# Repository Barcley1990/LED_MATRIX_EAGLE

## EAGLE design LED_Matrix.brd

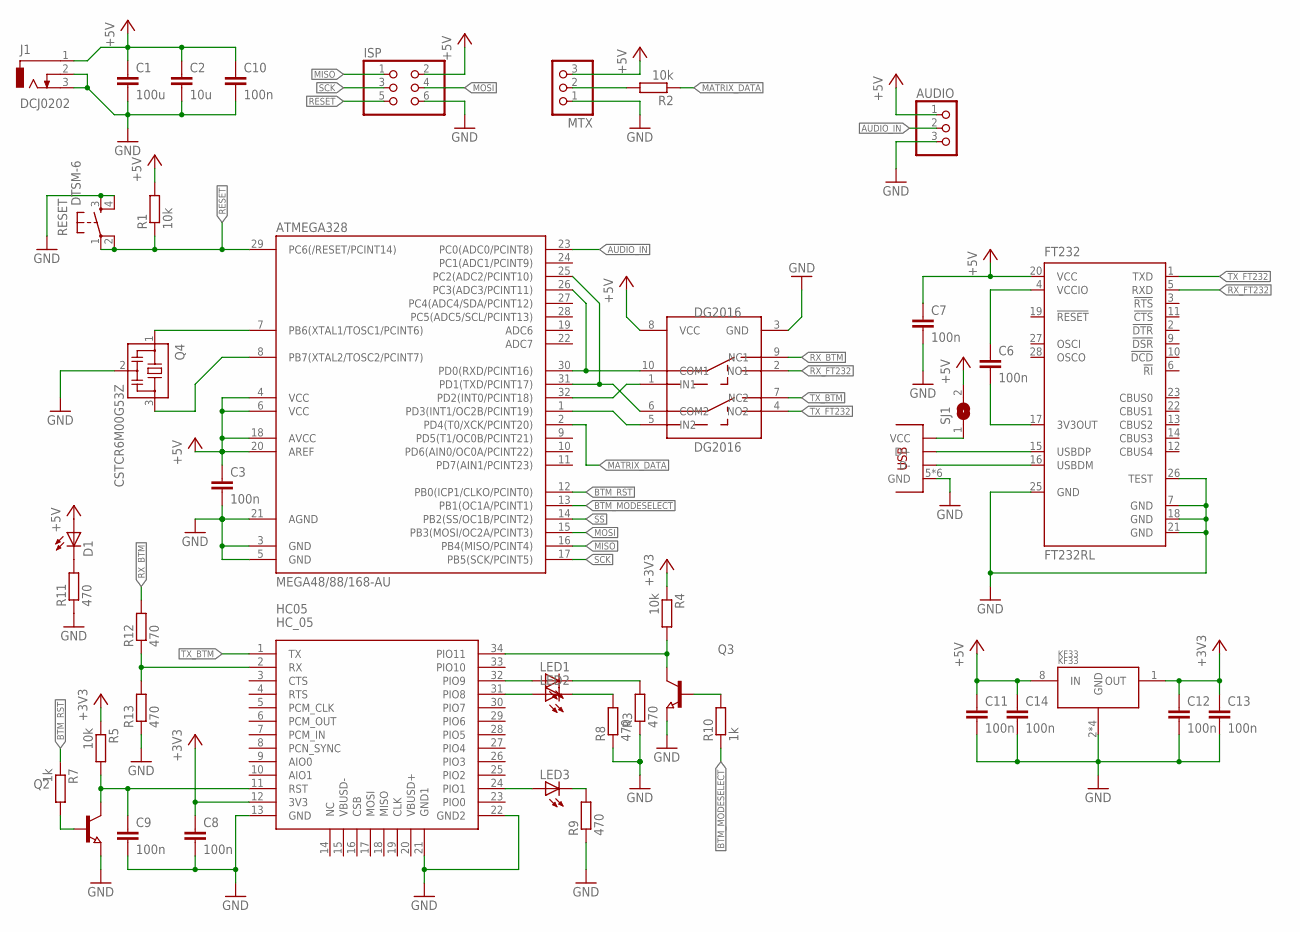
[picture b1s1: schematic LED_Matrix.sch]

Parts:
ATMEGA328: MEGA48/88/168-AU; TQFP32-08
AUDIO: PINHD-1X3; 1X03
C1: 100u; C0805
C2: 10u; C0805
C3, C6, C7, C8, C9, C10, C11, C12, C13, C14: 100n; C0805
D1: LEDSML0805; SML0805
DG2016: DG2016; MSOP10
FT232: FT232RL; SSOP28
HC05: HC_05; BLUETOOTH_SMD
ISP: PINHD-2X3; 2X03
J1: DCJ0202
KF33: KF33; SO08
LED1, LED2, LED3: LEDSML0805; SML0805
MTX: PINHD-1X3; 1X03
Q2, Q3: NPN-TRANSISTOR_SOT23; SOT23
Q4: CSTCR6M00G53Z; CSTCR6M
R1, R2, R4, R5: 10k; R0805
R3, R8, R9, R11, R12, R13: 470; R0805
R7, R10: 1k; R0805
RESET: DTSM-6
SJ1: SJ
USB: MINI_USB; USB_MINI

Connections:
+3V3: C8.1, C12.1, C13.1, HC05.12 (3V3), KF33.1 (OUT), R4.1, R5.1
+5V: ATMEGA328.4 (VCC), ATMEGA328.6 (VCC), ATMEGA328.18 (AVCC), ATMEGA328.20 (AREF), AUDIO.1, C1.1, C2.1, C3.1, C7.1, C10.1, C11.1, C14.1, D1.A, DG2016.8 (VCC), FT232.20 (VCC), ISP.2, J1.1, KF33.8 (IN), MTX.3, R1.2, SJ1.2
AUDIO_IN: ATMEGA328.23 (PC0(ADC0/PCINT8)), AUDIO.2
BTM_MODESELECT: ATMEGA328.13 (PB1(OC1A/PCINT1)), HC05.34 (PIO11), Q3.3 (C), R4.2, R10.1
BTM_RST: ATMEGA328.12 (PB0(ICP1/CLKO/PCINT0)), R7.1
GND: ATMEGA328.3 (GND), ATMEGA328.5 (GND), ATMEGA328.21 (AGND), AUDIO.3, C1.2, C2.2, C3.2, C7.2, C8.2, C9.2, C10.2, C11.2, C12.2, C13.2, C14.2, DG2016.3 (GND), FT232.7 (GND), FT232.18 (GND), FT232.21 (GND), FT232.25 (GND), FT232.26 (TEST), HC05.13 (GND), HC05.21 (GND1), HC05.22 (GND2), ISP.6, J1.2, J1.3, KF33.2 (GND), KF33.3 (GND), KF33.6 (GND), KF33.7 (GND), MTX.1, Q2.2 (E), Q3.2 (E), Q4.2, R3.1, R8.1, R9.1, R11.1, R13.1, RESET.3, RESET.4, USB.5 (GND), USB.GND, USB.GND1 (GND), USB.GND3 (GND), USB.GND4 (GND), USB.GND5 (GND)
MATRIX_DATA: ATMEGA328.2 (PD4(T0/XCK/PCINT20)), R2.1
MISO: ATMEGA328.16 (PB4(MISO/PCINT4)), ISP.1
MOSI: ATMEGA328.15 (PB3(MOSI/OC2A/PCINT3)), ISP.4
unnamed: HC05.32 (PIO9), LED1.A
unnamed: SJ1.1, USB.1 (VCC)
unnamed: ATMEGA328.7 (PB6(XTAL1/TOSC1/PCINT6)), Q4.1
unnamed: MTX.2, R2.2
unnamed: HC05.31 (PIO8), LED2.A
unnamed: LED1.C, R3.2
unnamed: ATMEGA328.8 (PB7(XTAL2/TOSC2/PCINT7)), Q4.3
unnamed: LED2.C, R8.2
unnamed: C6.1, FT232.4 (VCCIO)
unnamed: D1.C, R11.2
unnamed: C6.2, FT232.17 (3V3OUT)
unnamed: ATMEGA328.26 (PC3(ADC3/PCINT11)), ATMEGA328.30 (PD0(RXD/PCINT16)), DG2016.10 (COM1)
unnamed: FT232.16 (USBDM), USB.2 (D-)
unnamed: FT232.15 (USBDP), USB.3 (D+)
unnamed: ATMEGA328.25 (PC2(ADC2/PCINT10)), ATMEGA328.31 (PD1(TXD/PCINT17)), DG2016.6 (COM2)
unnamed: Q2.1 (B), R7.2
unnamed: C9.1, HC05.11 (RST), Q2.3 (C), R5.2
unnamed: HC05.24 (PIO1), LED3.A
unnamed: LED3.C, R9.2
unnamed: HC05.2 (RX), R12.1, R13.2
unnamed: Q3.1 (B), R10.2
unnamed: ATMEGA328.32 (PD2(INT0/PCINT18)), DG2016.1 (IN1)
unnamed: ATMEGA328.1 (PD3(INT1/OC2B/PCINT19)), DG2016.5 (IN2)
RESET: ATMEGA328.29 (PC6(/RESET/PCINT14)), ISP.5, R1.1, RESET.1, RESET.2
RX_BTM: DG2016.9 (NC1), R12.2
RX_FT232: DG2016.2 (NO1), FT232.5 (RXD)
SCK: ATMEGA328.17 (PB5(SCK/PCINT5)), ISP.3
SS: ATMEGA328.14 (PB2(SS/OC1B/PCINT2))
TX_BTM: DG2016.7 (NC2), HC05.1 (TX)
TX_FT232: DG2016.4 (NO2), FT232.1 (TXD)

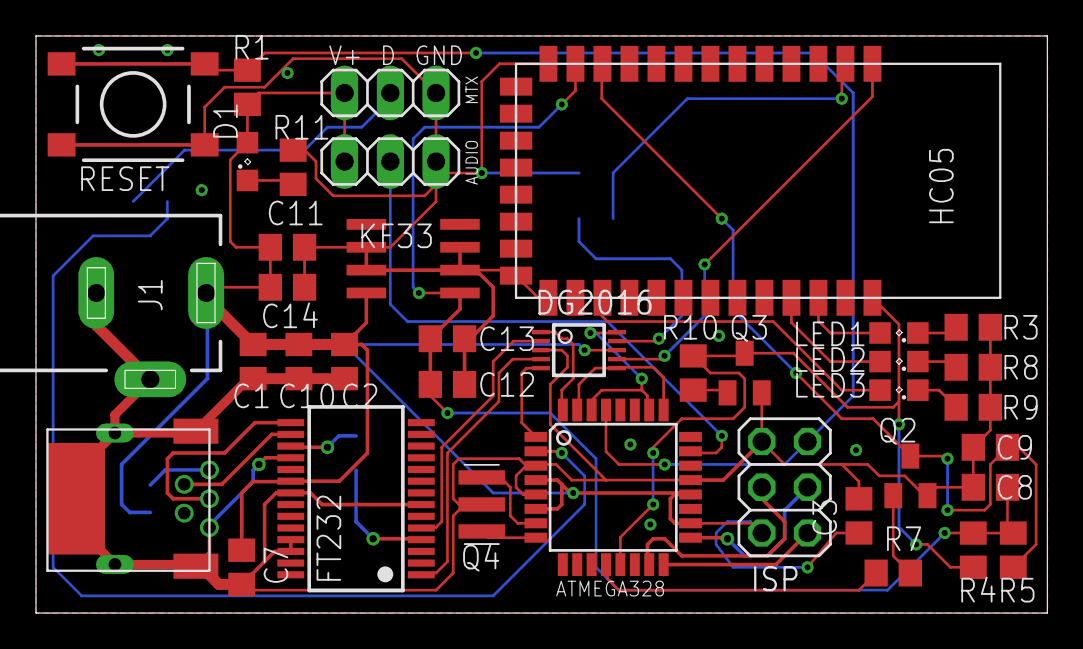
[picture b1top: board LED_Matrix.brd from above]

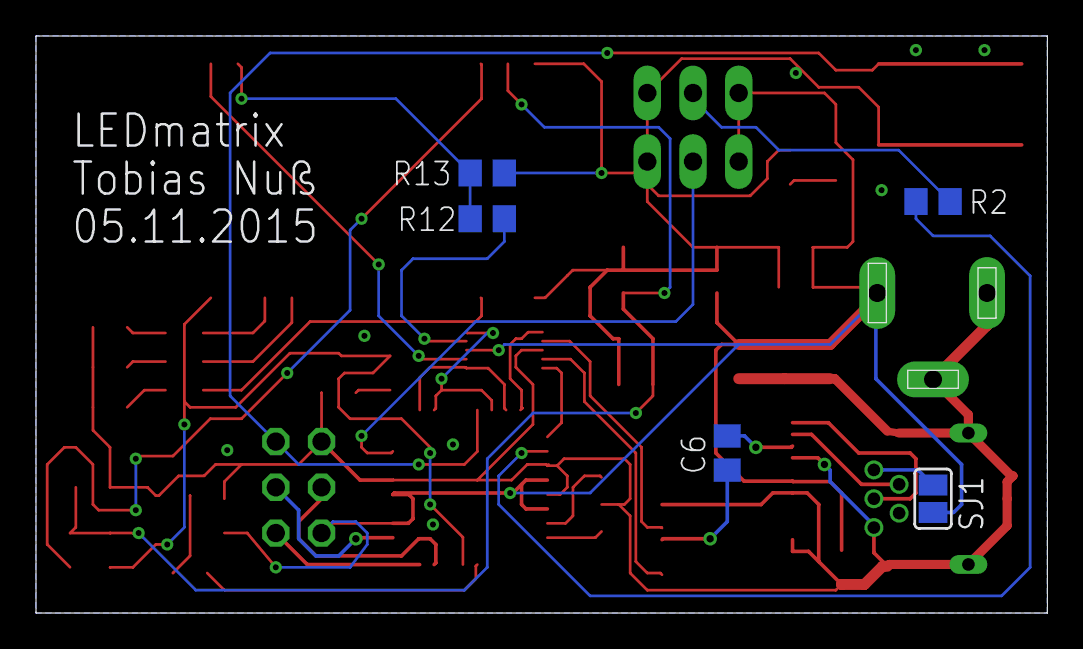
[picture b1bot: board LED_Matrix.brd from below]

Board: 2 copper layers, 56.2 x 32.1 mm, 43 parts (5 on the bottom side), 38 nets.

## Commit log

2015-10-22 initial commit.
2015-10-28 version 1
2015-10-28 analog switch added
2015-11-03 return point
2015-11-03 version 2 Final
2015-11-05 Audo in added
2015-11-05 added some GND Vias and Polygons
